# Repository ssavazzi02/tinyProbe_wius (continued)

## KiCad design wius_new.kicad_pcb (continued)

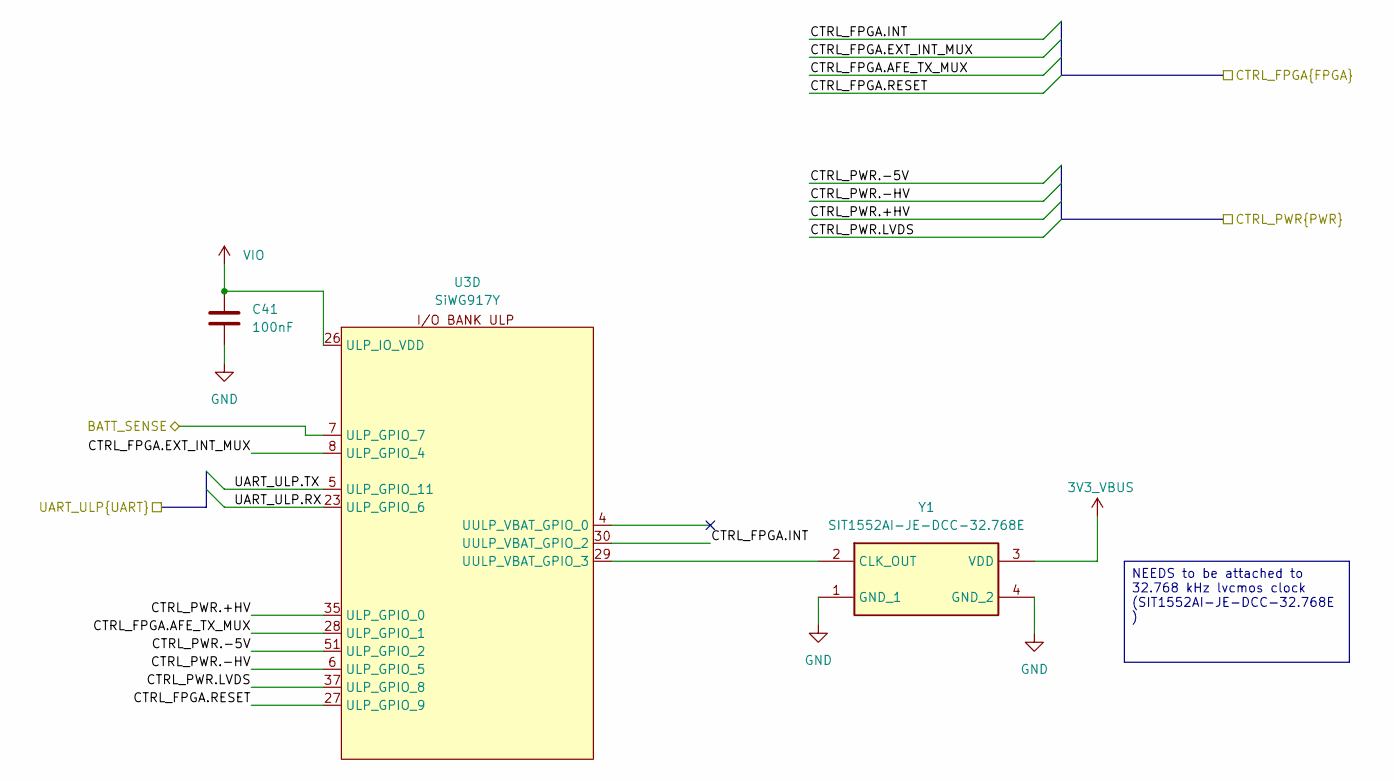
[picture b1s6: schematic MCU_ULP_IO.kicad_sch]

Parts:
C41: 100nF; C_0201_0603Metric; Voltage 10V; Tolerance 20%; MPN GRM033R61A104ME15
U3: SiWG917Y; Voltage 3.0V-3.63V; MPN SiWG917Y
Y1: SIT1552AI-JE-DCC-32.768E; SIT1552AIJEDCC32768E; MPN SIT1552AI-JE-DCC-32.768E; LCSC C7464055

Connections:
3V3_VBUS: Y1.3 (VDD); also elsewhere on the board
/DEBUG, RESET & POC_IN, PROGRAMMING INTERFACE/UART_ULP.RX: U3.23 (ULP_GPIO_6); also elsewhere on the board
/DEBUG, RESET & POC_IN, PROGRAMMING INTERFACE/UART_ULP.TX: U3.5 (ULP_GPIO_11); also elsewhere on the board
/MCU/BATT_SENSE: U3.7 (ULP_GPIO_7); also elsewhere on the board
/MCU/CTRL_FPGA.AFE_TX_MUX: U3.28 (ULP_GPIO_1); also elsewhere on the board
/MCU/CTRL_FPGA.EXT_INT_MUX: U3.8 (ULP_GPIO_4); also elsewhere on the board
/MCU/CTRL_FPGA.INT: U3.30 (UULP_VBAT_GPIO_2); also elsewhere on the board
/MCU/CTRL_FPGA.RESET: U3.27 (ULP_GPIO_9); also elsewhere on the board
/MCU/CTRL_PWR.+HV: U3.35 (ULP_GPIO_0); also elsewhere on the board
/MCU/CTRL_PWR.-5V: U3.51 (ULP_GPIO_2); also elsewhere on the board
/MCU/CTRL_PWR.-HV: U3.6 (ULP_GPIO_5); also elsewhere on the board
/MCU/CTRL_PWR.LVDS: U3.37 (ULP_GPIO_8); also elsewhere on the board
GND: C41.2, Y1.1 (GND_1), Y1.4 (GND_2); also elsewhere on the board
unnamed: U3.29 (UULP_VBAT_GPIO_3), Y1.2 (CLK_OUT)
VIO: C41.1, U3.26 (ULP_IO_VDD); also elsewhere on the board

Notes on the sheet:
NEEDS to be attached to 32.768 kHz lvcmos clock (SIT1552AI-JE-DCC-32.768E )

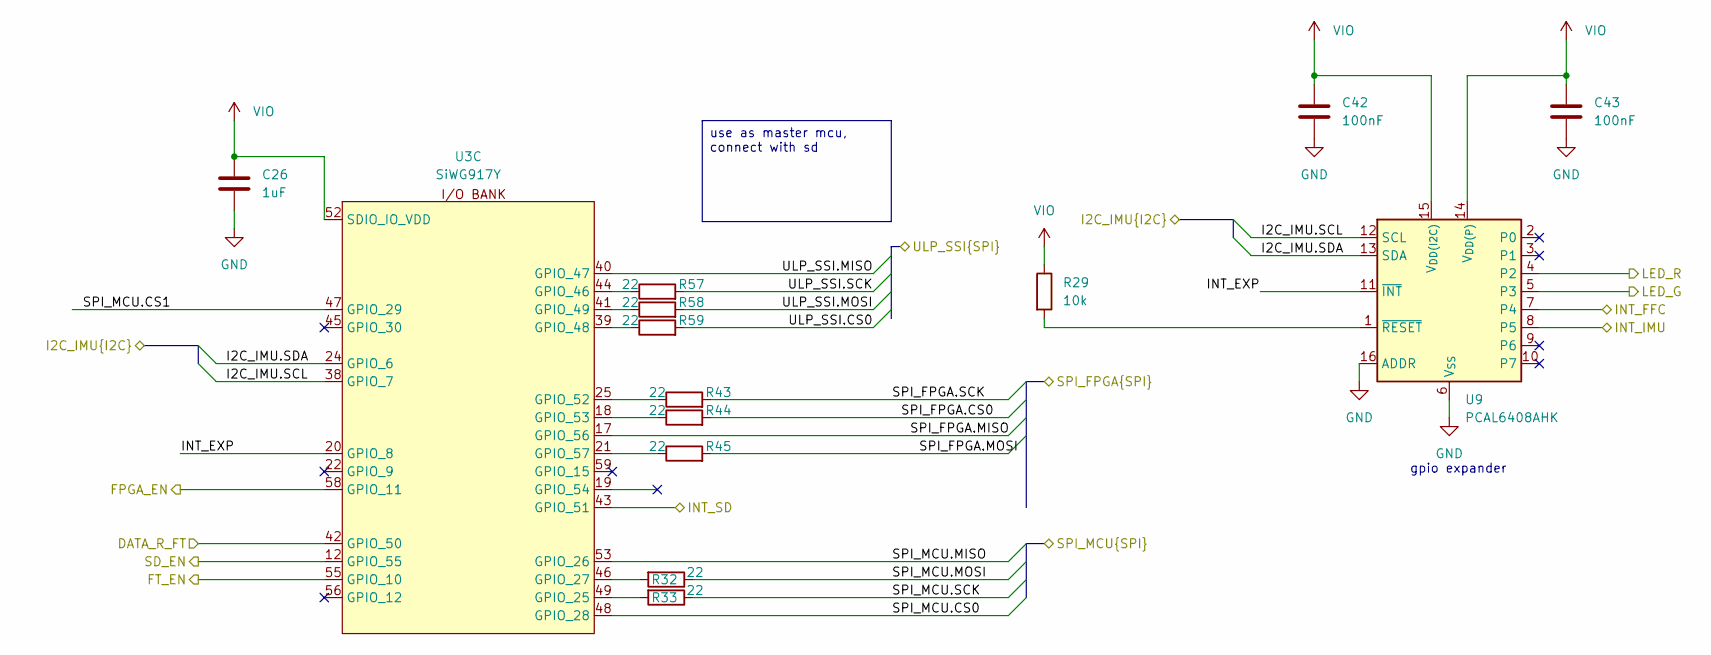
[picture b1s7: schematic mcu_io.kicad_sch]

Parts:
C26: 1uF; C_0402_1005Metric; Voltage 16V; Tolerance 20%; MPN GRM155R61C105MA12; LCSC C77009
C42, C43: 100nF; C_0201_0603Metric; Voltage 10V; Tolerance 20%; MPN GRM033R61A104ME15
R29: 10k; R_0402_1005Metric; Tolerance 1%; MPN ERJ-2RKF1002X; LCSC C191123
R32, R33: 22; R_0402_1005Metric; Tolerance 1%; MPN ERJ-2RKF22R0X; LCSC C413049
R43, R44, R45, R57, R58, R59: 22; R_0201_0603Metric; Tolerance 1%; MPN ERJ-1GJF22R0C; LCSC C20021234
U3: SiWG917Y; Voltage 3.0V-3.63V; MPN SiWG917Y
U9: PCAL6408AHK; UQFN-16_1.8x2.6mm_P0.4mm; MPN PCAL6408AHK; LCSC C5203525

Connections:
/DEBUG, RESET & POC_IN, PROGRAMMING INTERFACE/LED_G: U9.5 (P3); also elsewhere on the board
/DEBUG, RESET & POC_IN, PROGRAMMING INTERFACE/LED_R: U9.4 (P2); also elsewhere on the board
/IMU_SD/I2C_IMU.SCL: U3.38 (GPIO_7), U9.12 (SCL); also elsewhere on the board
/IMU_SD/I2C_IMU.SDA: U3.24 (GPIO_6), U9.13 (SDA); also elsewhere on the board
/IMU_SD/INT_IMU: U9.8 (P5); also elsewhere on the board
/IMU_SD/INT_SD: U3.43 (GPIO_51); also elsewhere on the board
/IMU_SD/SD_EN: U3.12 (GPIO_55); also elsewhere on the board
/IMU_SD/SPI_MCU.CS0: U3.48 (GPIO_28); also elsewhere on the board
/IMU_SD/SPI_MCU.CS1: U3.47 (GPIO_29); also elsewhere on the board
/IMU_SD/SPI_MCU.MISO: U3.53 (GPIO_26); also elsewhere on the board
/IMU_SD/SPI_MCU.MOSI: R32.1; also elsewhere on the board
/IMU_SD/SPI_MCU.SCK: R33.1; also elsewhere on the board
/MCU/DATA_R_FT: U3.42 (GPIO_50); also elsewhere on the board
/MCU/FPGA_EN: U3.58 (GPIO_11); also elsewhere on the board
/MCU/FT_EN: U3.55 (GPIO_10); also elsewhere on the board
/MCU/INT_FFC: U9.7 (P4); also elsewhere on the board
/MCU/MCU_IO/INT_EXP: U3.20 (GPIO_8), U9.11 (~INT)
/MCU/SPI_FPGA.CS0: R44.2; also elsewhere on the board
/MCU/SPI_FPGA.MISO: U3.17 (GPIO_56); also elsewhere on the board
/MCU/SPI_FPGA.MOSI: R45.2; also elsewhere on the board
/MCU/SPI_FPGA.SCK: R43.2; also elsewhere on the board
/MCU/ULP_SSI.CS0: R59.2; also elsewhere on the board
/MCU/ULP_SSI.MISO: U3.40 (GPIO_47); also elsewhere on the board
/MCU/ULP_SSI.MOSI: R58.2; also elsewhere on the board
/MCU/ULP_SSI.SCK: R57.2; also elsewhere on the board
GND: C26.2, C42.2, C43.2, U9.6 (V_{SS}), U9.16 (ADDR); also elsewhere on the board
unnamed: R33.2, U3.49 (GPIO_25)
unnamed: R32.2, U3.46 (GPIO_27)
unnamed: R57.1, U3.44 (GPIO_46)
unnamed: R59.1, U3.39 (GPIO_48)
unnamed: R58.1, U3.41 (GPIO_49)
unnamed: R43.1, U3.25 (GPIO_52)
unnamed: R44.1, U3.18 (GPIO_53)
unnamed: R45.1, U3.21 (GPIO_57)
unnamed: R29.2, U9.1 (~RESET)
VIO: C26.1, C42.1, C43.1, R29.1, U3.52 (SDIO_IO_VDD), U9.14 (V_{DD(P)}), U9.15 (V_{DD(I2C)}); also elsewhere on the board

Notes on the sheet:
gpio expander
use as master mcu, connect with sd

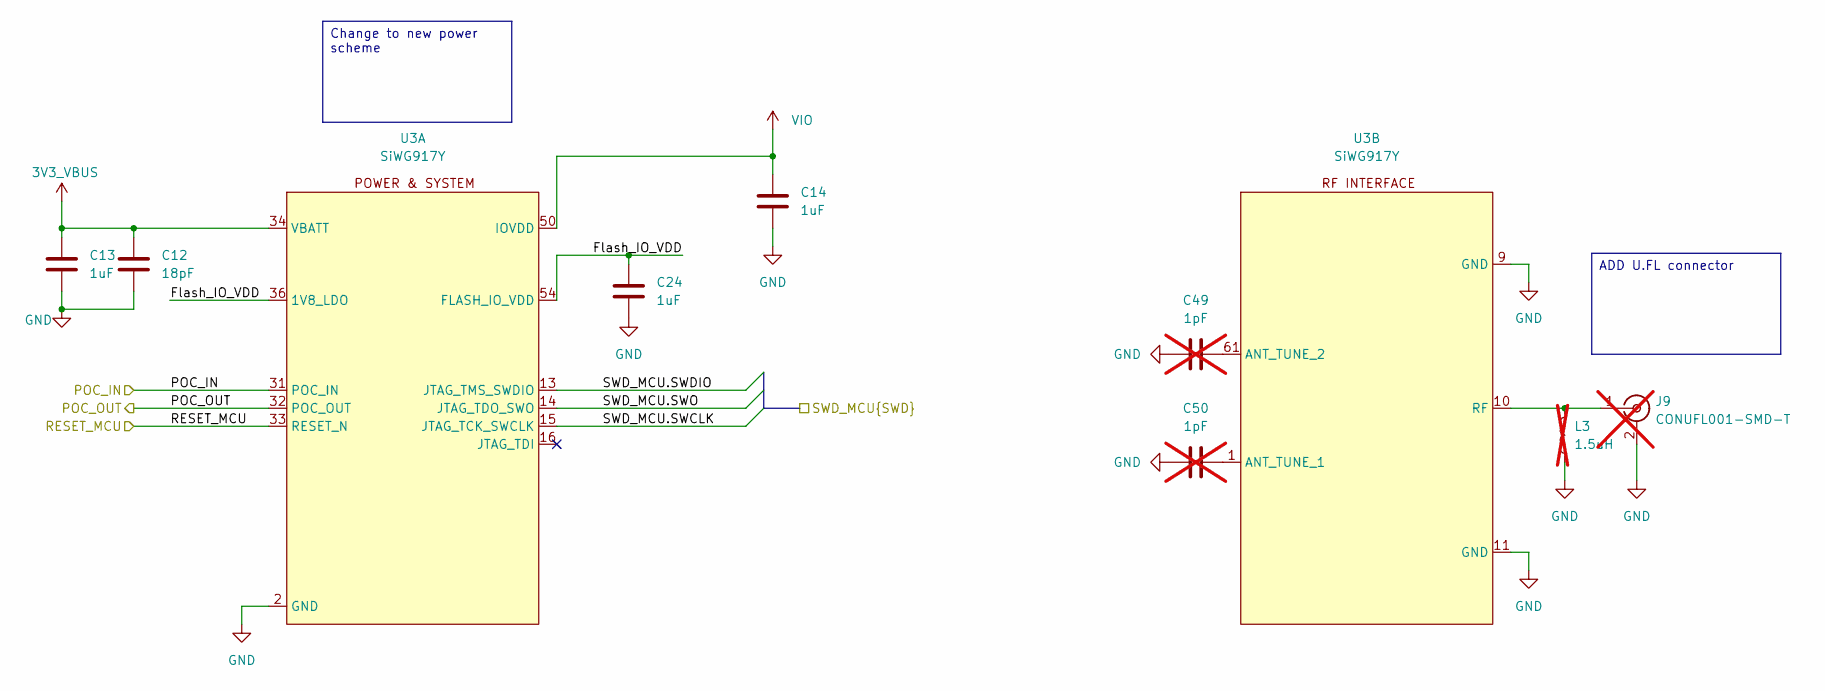
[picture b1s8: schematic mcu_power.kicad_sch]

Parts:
C12: 18pF; C_0402_1005Metric; Tolerance 5%; Voltage 50V; MPN GRM1555C1H180JA01; LCSC C33149
C13, C14, C24: 1uF; C_0402_1005Metric; Voltage 16V; Tolerance 20%; MPN GRM155R61C105MA12; LCSC C77009
C49, C50: 1pF; C_0402_1005Metric; Voltage 50V; Tolerance ±0.25pF; MPN GRM1555C1H1R0CA01; LCSC C76953; not fitted
J9: U.FL; U.FL_Hirose_U.FL-R-SMT-1_Vertical; MPN CONUFL001-SMD-T; LCSC C41432122; not fitted
L3: 1.5uH; L_0805_2012Metric; MPN 0805LS-152GRC; LCSC C40455103; not fitted
U3: SiWG917Y; Voltage 3.0V-3.63V; MPN SiWG917Y

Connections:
3V3_VBUS: C12.1, C13.1, U3.34 (VBATT); also elsewhere on the board
/DEBUG, RESET & POC_IN, PROGRAMMING INTERFACE/SWD_MCU.SWCLK: U3.15 (JTAG_TCK_SWCLK); also elsewhere on the board
/DEBUG, RESET & POC_IN, PROGRAMMING INTERFACE/SWD_MCU.SWDIO: U3.13 (JTAG_TMS_SWDIO); also elsewhere on the board
/DEBUG, RESET & POC_IN, PROGRAMMING INTERFACE/SWD_MCU.SWO: U3.14 (JTAG_TDO_SWO); also elsewhere on the board
/MCU/MCU_POWER_RF/Flash_IO_VDD: C24.1, U3.36 (1V8_LDO), U3.54 (FLASH_IO_VDD)
/MCU/MCU_POWER_RF/POC_IN: U3.31 (POC_IN); also elsewhere on the board
/MCU/MCU_POWER_RF/POC_OUT: U3.32 (POC_OUT); also elsewhere on the board
/MCU/MCU_POWER_RF/RESET_MCU: U3.33 (RESET_N); also elsewhere on the board
GND: C12.2, C13.2, C14.2, C24.2, C49.1, C50.1, J9.2 (Ext), L3.1, U3.2 (GND), U3.3 (GND), U3.9 (GND), U3.11 (GND), U3.57 (GND), U3.60 (GND), U3.62 (GND), U3.63 (GND), U3.64 (GND), U3.65 (GND), U3.66 (GND), U3.67 (GND), U3.68 (GND), U3.69 (GND), U3.70 (GND), U3.71 (GND); also elsewhere on the board
unnamed: J9.1 (In), L3.2, U3.10 (RF)
unnamed: C50.2, U3.1 (ANT_TUNE_1)
unnamed: C49.2, U3.61 (ANT_TUNE_2)
VIO: C14.1, U3.50 (IOVDD); also elsewhere on the board

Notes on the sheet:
Change to new power scheme
ADD U.FL connector

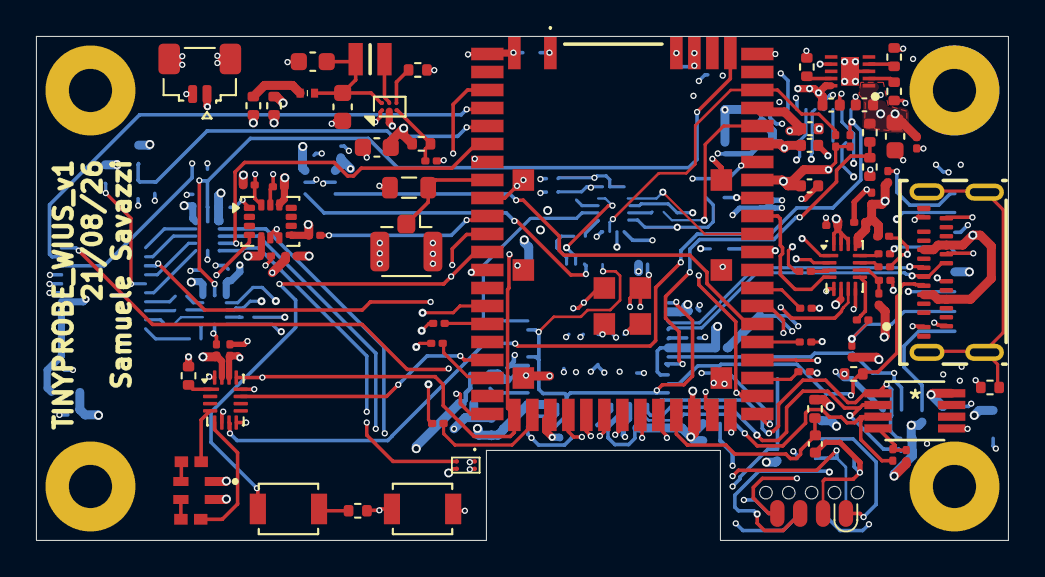
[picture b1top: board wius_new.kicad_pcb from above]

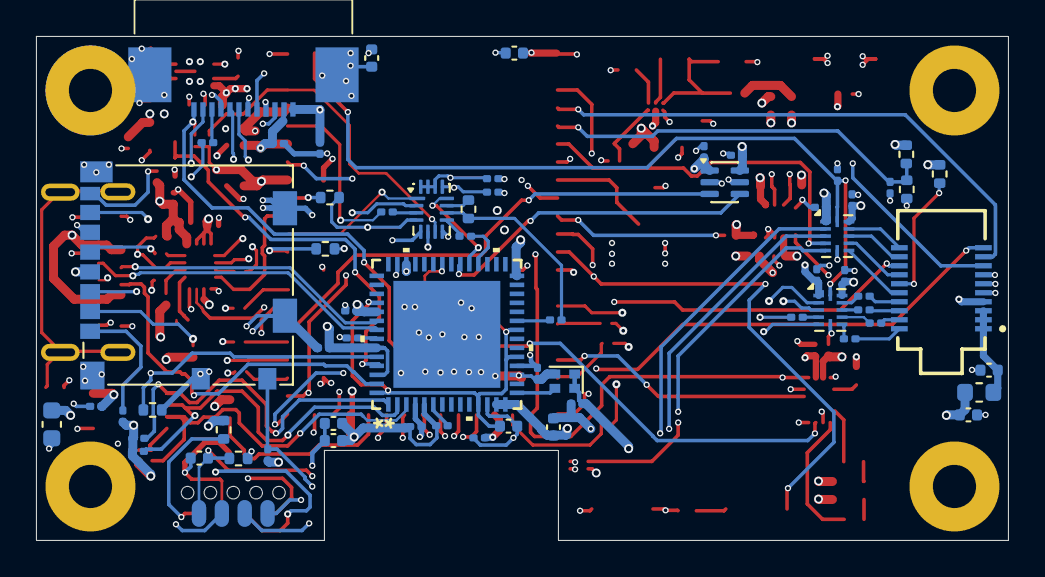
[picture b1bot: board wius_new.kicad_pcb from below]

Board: 6 copper layers, 54.0 x 28.0 mm, 142 parts (63 on the bottom side), 122 nets.

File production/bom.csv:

Designator,Footprint,Quantity,Value,LCSC Part #
"C1, C13, C14, C24, C26, C3",0402,6,1uF,C77009
"C10, C11, C15, C16, C17, C18, C20, C21, C22, C25, C28, C30, C31, C32, C34, C35, C36, C37, C38, C39, C40, C41, C42, C43, C44, C6",0201,26,100nF,GRM033R61A104ME15
"C114, C115",0402,2,10uF,C408132
C12,0402,1,18pF,C33149
"C19, C23",0402,2,4.7uF,C2858031
"C2, C27, C7, C8, C9",0603,5,10uF,C197020603
"C29, C33",0402,2,10nF,C91601
C4,0201,1,1uF,C274414
D1,LED_APTB1615SURKCGKC-F01,1,APTB1615SURKCGKC-F01,C5879208
FB2,0603,1,100Ω@100MHz,C3717002
FB6,BLM15KD121SN1D,1,120Ω@100MHz,C710343
IC1,BQ24040DSQT,1,BQ24040DSQT,C2876332
J2,527461271,1,52746-1271,C588231
J3,microSD_HC_Molex_104031-0811,1,1040310811,C585350
J4,SAMTEC_SS5_10_3.00_X_D_K_XX,1,SS5-10-3.00-L-D-K-TR,C7087204
J5,GTC_USB4745,1,USB4745-03-A,C2911517
J8,JST_SUR_SM02B-SURS-TF_1x02-1MP_P0.80mm_Horizontal,1,2,SM02B-SURS-TF(LF)(SN)
L9,DFE2MCAH2R2MJ0L,1,2.2uH,C2045354
R1,0402,1,1.1k,C853096
"R10, R11, R13, R14, R17, R20, R28, R31, R34, R38, R39, R63, R8",0201,13,10k,C20021044
"R12, R6",0402,2,1k,C242161
"R15, R16",0402,2,5.1k,C278598
R18,0402,1,6.65k,C185400
"R19, R21",RESC1005X40N,2,280,C273692
R2,0402,1,2k,C853619
"R22, R29",0402,2,10k,C191123
R23,0402,1,100,C413063
"R24, R3, R4, R51",0402,4,0,C17168
"R25, R26, R27, R30",0402,4,100k,C192169
"R32, R33",0402,2,22,C413049
R35,0402,1,220k,C413112
"R36, R37, R41, R42, R43, R44, R45, R47, R48, R49, R5, R52, R53, R54, R55, R56, R57, R58, R59, R60",0201,20,22,C20021234
"R40, R61, R62",0201,3,100k,C20021045
R46,0201,1,2.2k,C20021223
R7,0402,1,1M,C413126
R9,0201,1,12k,C20021084
"SW3, SW4",SW_SPST_B3U-1000P,2,Button Switch SPST-No,C231329
U1,Texas_DSBGA-6_0.9x1.4mm_Layout2x3_P0.5mm,1,TPS62840YBGR,1.5MHz-2.5MHz
U10,MSOP8_MC_MCH,1,93LC66B-I/MS,93LC66B-I/MS
U12,SOT-363_SC-70-6,1,SN74LVC1T45DCK,
"U13, U2",Texas_R-PUQFN-N12,2,TXB0104RUT,
U3,SiWG917Y,1,SiWG917Y,~
U4,QFN-56_FT232HPQ_FTD,1,FT232HPQ,C3227934
U5,LGA-14_3x2.5mm_P0.5mm_LayoutBorder3x4y,1,LSM6DSV,C5267399
"U6, U8",UQFN-16_1.8x2.6mm_P0.4mm,2,SN74AXC4T774RSVR,C1849454
U7,SOIC_clipProgSmall,1,SOIC_clipProgSmall,
U9,UQFN-16_1.8x2.6mm_P0.4mm,1,PCAL6408AHK,C5203525
Y1,SIT1552AIJEDCC32768E,1,SIT1552AI-JE-DCC-32.768E,C7464055
Y2,Oscillator_SMD_Abracon_ASCO-4Pin_1.6x1.2mm,1,ASCO-12.000MHZ-EK-T3,ASCO-12.000MHZ-EK-T3

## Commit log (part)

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2026-06-05 Inizializzazione progetto wearable: configurazione base KiCad e .gitignore
2026-06-05 pulizia repo senza backup e history
2026-06-05 Rimossa repository embedded .history derivata dal progetto open source
2026-06-05 Rimossa definitivamente la cartella dei backup dal server
2026-06-11 insert of gpio expander
2026-06-12 added schematics comments of review 1
2026-06-13 Salvataggio locale prima del pull
2026-06-18 changes after first review: add lvl shifters, board at 1v8, new power tree
2026-06-25 updated schematic and initial pcb placement
2026-06-25 upload of 3d models used in pcb document
